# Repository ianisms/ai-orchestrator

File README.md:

# ai-orchestrator

This is a fully local voice assistant. A custom smart speaker built on a Raspberry Pi CM5 talks to a GPU server over one bidirectional gRPC stream. Speech recognition, the language model, tool calling, and speech synthesis all run on hardware in the house. Nothing in the audio path touches a cloud API.

This repository is a sanitized snapshot of a personal project, published as a reference for how I design and build systems. It is not packaged for reuse; there is no one-command install. It does show a working end-to-end system with the tradeoffs left visible. It has streaming everywhere, barge-in, per-speaker identity, an MCP tool plane with authorization boundaries, and observability from the first commit.

I am Ian Bennett ([github.com/ianisms](https://github.com/ianisms)). The source is available for review under the PolyForm Strict License 1.0.0. Any other use needs my written permission. See [LICENSE.md](LICENSE.md) and [NOTICE](NOTICE).

## What is here

| Path | What it is |
|---|---|
| [`server/`](server/README.md) | GPU server: gRPC orchestrator, MCP tools server and proxy, custom TTS service, Docker Compose stack with Prometheus, Grafana, and Loki |
| [`speaker/`](speaker/README.md) | Pi CM5 voice client (wakeword, VAD, capture, playback, barge-in), device tree overlay, bring-up scripts, custom KiCad carrier board, 3D-printed enclosure |
| [`DESIGN_NOTES.md`](DESIGN_NOTES.md) | Design notes with file references |
| [`security/`](security/README.md) | Agent identity and authorization prototypes: token exchange delegation, revocation, a policy check before every tool call with the policy grammar in Rego, voice step-up rules, threat model |

Everything in `server/` is Python 3.11 with `asyncio`, gRPC, FastMCP, FastAPI, and NVIDIA NeMo. The speaker client is Python on Raspberry Pi OS in a Docker container with ALSA passthrough. Hardware sources are KiCad 9 and STEP.

## Architecture

```mermaid
flowchart LR
    subgraph Speaker["Smart speaker (Pi CM5)"]
        MIC[XVF3800 mic array<br/>I2S capture] --> WW[Wakeword<br/>openWakeWord]
        WW --> VAD[Adaptive VAD<br/>+ preroll]
        VAD --> GC[gRPC client]
        GC --> PB[Playback worker<br/>+ barge-in monitor]
        PB --> AMP[JAB5 DSP amp<br/>I2S playback]
    end

    GC <-->|"Converse<br/>bidirectional stream"| ORCH

    subgraph Server["GPU server (Ryzen 9 / RTX PRO 6000)"]
        ORCH[Orchestrator<br/>:7000 gRPC]
        ORCH --> STT[STT<br/>Parakeet CTC NIM]
        ORCH --> LLM[LLM<br/>Qwen3 on vLLM]
        ORCH --> TTS[TTS<br/>FastPitch + HiFi-GAN]
        ORCH <--> TOOLS[Tools server<br/>FastMCP :9102]
        TOOLS --> LOCAL[20 local tools<br/>weather, places, identity, ...]
        TOOLS --> PROXY[MCP proxy]
        PROXY --> HA[Home Assistant<br/>MCP server]
        ORCH -.-> OBS[Prometheus / Grafana / Loki]
        TOOLS -.-> OBS
        TTS -.-> OBS
    end
```

One turn runs end to end like this. The speaker hears the wakeword, plays a chime, and streams 16 kHz PCM frames to the orchestrator. The orchestrator forwards audio to the STT service as it arrives and starts a speculative LLM call on partial transcripts. When the utterance commits, the LLM streams a reply. Any tool calls in it are validated locally, dispatched in parallel over MCP, and folded back into a second low-temperature synthesis pass. Reply text is sanitized for speech and streamed to the TTS service. The TTS service returns PCM that the orchestrator relays to the speaker in chunks. If the user talks over the reply, the speaker detects it, sends `Cancel`, and the server tears down TTS mid-stream.

## Things worth reading

These are the parts I would point a reviewer at first. [`DESIGN_NOTES.md`](DESIGN_NOTES.md) has the full list with file references.

**Audio never crosses the tool protocol.** Speaker identification needs the turn's audio, but base64-encoding seconds of PCM through JSON-RPC is the wrong shape. The orchestrator instead wraps the STT input queue in a duck-typed `AudioTapQueue`. It records frames in passing, writes a WAV on commit, and injects an opaque `[AUDIO_REF session_id audio_id]` into the prompt. The identity tool reads the file from a shared mount. There is zero copy on the hot path, and the reference is bound to this turn so it cannot be replayed. ([`server/modules/orchestrator/core/audio_tap.py`](server/modules/orchestrator/core/audio_tap.py))

**Authorization boundaries the model cannot cross.** Two kinds of state are scoped by values the LLM never supplies. `client_id` for per-device preferences comes from the gRPC peer, and person identity comes from the current turn's audio. The MCP proxy enforces per-upstream `allowed_tools` and `denied_tools`, and deny wins. It namespaces upstream tools as `server__tool` so nothing collides. It unregisters a server's tools when its liveness ping fails, so the model never sees a tool it cannot call. Tool arguments are validated against JSON Schema locally before dispatch. Unknown tool names are dropped and never called. ([`server/tools_server/mcp_proxy.py`](server/tools_server/mcp_proxy.py), [`server/modules/orchestrator/core/utterance.py`](server/modules/orchestrator/core/utterance.py))

**Agent identity prototypes, built next to the assistant.** `security/` holds standalone prototypes for the next layer of that boundary. RFC 8693 token exchange carries the whole agent chain (user > gateway > sub-agent) in an `act` claim. An AuthZEN-shaped policy check in OPA runs before every `tools/call` and fails closed. Voice step-up rules cover the speaker match threshold, home-network origin, liveness, and confirmation on by default and mandatory for high-risk tools. A threat model lists the attacks run against them. The delegation and policy prototypes still run on their own. The voice rules also run inside the orchestrator as a gate in front of every tool call, in monitor mode until the liveness check and approval channels exist ([`server/modules/orchestrator/core/voice_gate.py`](server/modules/orchestrator/core/voice_gate.py)). CI runs the security and voice gate tests on every pull request, and the check is required on `main`. ([`security/README.md`](security/README.md), [`security/THREAT_MODEL.md`](security/THREAT_MODEL.md))

**Hot reload propagated end to end.** Save a tool file on the server and the LLM's tool list updates without restarting anything. `watchfiles` triggers an unregister-then-reload in the tools server. The tools server pushes a `ToolListChangedNotification` to every live MCP transport. The orchestrator's client picks it up and refreshes asynchronously. ([`server/tools_server/loader.py`](server/tools_server/loader.py), [`server/modules/orchestrator/tools/mcp_client.py`](server/modules/orchestrator/tools/mcp_client.py))

**Upstream MCP schemas rewritten from YAML.** Home Assistant's MCP tool descriptions were written for a chat UI. A voice model has to pick `name`, `area` or `floor` in one shot and needs something tighter. `mcp-servers.yaml` overrides descriptions and entire parameter schemas per upstream tool without forking the upstream server, and stamps provenance into tool metadata. The proxy also carries a transport subclass because Home Assistant needs `POST` for its SSE stream. ([`server/tools_server/mcp-servers.yaml`](server/tools_server/mcp-servers.yaml), [`server/tools_server/mcp_proxy.py`](server/tools_server/mcp_proxy.py))

**Degrade before evict.** Under session pressure the orchestrator shrinks every session's history token budget instead of dropping conversations. It only hard-evicts LRU above a separate 1.25x cap. The budget itself is negotiated from the model's real `max_model_len` at startup. Config can lower it but never overflow the context. ([`server/modules/aiserver/server.py`](server/modules/aiserver/server.py))

**Barge-in on both ends.** Server side, any inbound audio frame while `SPEAKING` sets an `asyncio.Event` that doubles as the TTS cancel token. Client side, a dedicated VAD instance watches the mic only during playback. A stale-queue drain and a 600 ms chime-bleed guard keep it from triggering on its own output. The client also has a documented late-cancel path. The receive loop polls the cancel event because the transmit task has already exited after end-of-utterance. ([`speaker/modules/speaker/capture_streamer.py`](speaker/modules/speaker/capture_streamer.py), [`speaker/modules/speaker/grpc_client.py`](speaker/modules/speaker/grpc_client.py))

**Three queues, three overflow policies.** Inbound audio and text drop the oldest. The outbound queue evicts the oldest and records which message kind was dropped. On the speaker, the `control` event topic is unbounded while telemetry topics drop. Losing a wakeword or barge-in event is unacceptable. Losing a stats event is fine. ([`server/modules/aiserver/server.py`](server/modules/aiserver/server.py), [`speaker/modules/speaker/events_bus.py`](speaker/modules/speaker/events_bus.py))

**Prosody-aware TTS streaming.** The TTS service chunks on sentence boundaries and merges tiny trailing fragments backwards because they synthesize badly. It crossfades chunks with an equal-power window and inserts real silence at sentence ends. Text normalization runs under a 150 ms budget and falls back to raw text, so it is never a latency floor. A single GPU lock serializes synthesis because the LLM, STT, and TTS share one card. ([`server/tts/server/`](server/tts/server/))

**Proto drift shows up as a warning.** The server hashes its own `.proto` at startup and exchanges the SHA in gRPC metadata. Skew between the Pi and the server shows up as one log line instead of a deserialization bug three layers down. ([`server/modules/aiserver/server.py`](server/modules/aiserver/server.py))

## Hardware

The speaker is a Raspberry Pi CM5 on a custom carrier board ([`speaker/hardware/pcb/theboard/`](speaker/hardware/pcb/theboard/), KiCad, revision 3.7). An XMOS XVF3800 four-mic array captures over I2S and a Wondom JAB5 (ADAU1701 DSP) amplifier plays back over the same bus. The Pi is bitclock and frame master for both. A single device tree overlay ([`speaker/overlays/xvf3800-jab5-i2s.dts`](speaker/overlays/xvf3800-jab5-i2s.dts)) exposes them as one ALSA card with capture and playback. Power is an internal Mean Well 28 V supply with a captive AC cord. The enclosure ([`speaker/enclosure/`](speaker/enclosure/guide/guide.md)) is 3D printed with a wood veneer wrap. STEP solids and the build guide are included.

[`speaker/README.md`](speaker/README.md) has the wiring table, power architecture, and bring-up sequence.

## Running it

This is not turnkey, but the pieces are all here. The server expects an NVIDIA GPU with enough VRAM for the three inference services, Docker with the NVIDIA container toolkit, and model weights under `/ai/server/` as described in [`server/README.md`](server/README.md). Copy `server/.env.example` to `.env` and fill in the API keys for whichever tools you enable. `docker compose up` in `server/docker/` brings up the stack with health-gated dependency ordering.

The speaker client is built and deployed with `speaker/scripts/build_pi_release.sh` and `deploy_pi_release_wsl.sh`. See [`speaker/README.md`](speaker/README.md).

## What was removed for publication

Secrets were never committed. These were stripped or generalized:

- LAN addresses and hostnames
- personal contact details and example locations
- the local model directory name
- the system prompt persona
- AI coding-assistant session files
- an earlier generation of the speaker client
- PCB revisions 3.5 and 3.6 and the fabrication order files
- large generated artifacts (STEP exports of the PCB, footprint caches)

The custom TTS voice model, the custom wakeword model, and their training data are not included; the wakeword config defaults to a public openWakeWord model. Git history was not carried over.

## Author

Ian Bennett is a principal engineer and architect with 27 years in software, most recently at Microsoft on Azure Identity Governance and Azure Customer Lockbox. This project is where the identity and authorization thinking from that work meets a soldering iron.

## Decisions and division of labor

This repo was built the way I build now. I set the design and the rules. Claude (Claude Code and the Claude app) wrote most of the implementation, tests and docs against those designs. I reviewed, pushed back, and merged. The design calls below are mine. Where an agent proposed something I rejected or changed, the final shape is what is in the tree.

- The model never supplies its own identity. Speaker identity comes from the turn's audio. Origin comes from the device credential the speaker proved with its hardware key, or from the gRPC peer until that is required. Neither ever comes from headers or from anything the model says. Saying "I'm Alice" queues an enrollment sample for out-of-band approval and never changes a profile. New voices are enrolled in an admin-run session with prompted sentences and a separation check against the other voices in the house ([`security/VOICE_ENROLLMENT.md`](security/VOICE_ENROLLMENT.md)).
- The voice gate takes a strong speaker match, device origin and a liveness check as policy inputs. Confirmation is on by default and never waivable for high-risk tools. Unknown tools are treated as writes. Any missing signal denies. It rolled out in monitor mode first, with enforce after calibration, the same way I onboarded services to Customer Lockbox.
- Agents pass delegation, never credentials. Every hop exchanges for its own tokens with its own identity. Scope only narrows down the chain, depth is capped, and tools reject tokens without the `act` chain.
- Revocation cuts the narrowest thing first: a token, then a grant, then a client. The user token's `grant_id` travels unchanged down the chain, so revoking it kills the whole family. That closes a gap Keycloak leaves open. Tool servers can report a token with a reason, and the STS decides whether a report escalates.
- No stored secrets where federation can replace them. A tool that cannot speak OAuth sits behind a proxy that can. The proxy fetches the native credential per call and holds nothing at rest. Every remaining static secret carries a migration date.
- One broker surface for agents, with adapters underneath that use each platform's workload identity where it exists and our own where it does not. Agents never carry per-platform code.
- Device identity for the speaker is a plugged-in YubiKey now, because it ships this month, and then a TPM 2.0 on the PCB of the next carrier-board revision. I design the board, and a part on the board beats a dongle.
- The enclosure design is entirely mine. The CM5 carrier board was a joint effort. I authored the KiCad files, schematic and layout, and Claude advised on component selection.
- Publication is a sanitized single-commit copy of the private repos, with the MAUI client left out and PolyForm Strict in place of MIT so the code is usable only with my consent.

Claims were checked against the tree in both directions. When my description outran the code (the voice gate rules, before the gate existed), the gap became a backlog item and then the prototype. When a doc outran the code (an attestation story that called network origin plus voice "attestation"), the doc was cut back to what is true.

Three things are still unproven. The YubiKey signer has not run on hardware. The device credential is not yet enforced on the gRPC stream. The voice gate is in monitor mode. I would sooner say that here than have you find it.

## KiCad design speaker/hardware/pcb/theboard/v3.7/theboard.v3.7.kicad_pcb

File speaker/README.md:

# Smart speaker

This is the voice client and hardware for a fully local voice assistant. A Raspberry Pi Compute Module 5 on a custom carrier board captures audio from an XMOS XVF3800 mic array over I2S. It streams the audio to the AI server over gRPC and plays the reply through a Wondom JAB5 DSP amplifier on the same I2S bus. There is no cloud dependency anywhere in the audio path.

## Voice flow

1. The client listens continuously for a wakeword with openWakeWord. The deployed unit uses a custom phrase trained with the [openWakeWord training notebook](https://github.com/dscripka/openWakeWord#training-new-models). That model is not included. `wake_model_path` defaults to the bundled `hey_jarvis` model, which `docker/oww_bootstrap.py` downloads at image build.
2. On wake it plays a chime and begins streaming the utterance. A pre-roll buffer keeps the audio from just before the wake event so the first syllable is not clipped.
3. Energy-based adaptive VAD gates the stream. Capture ends on sustained silence, or early when the server reports `THINKING` or sends the first TTS chunk.
4. The server streams `Transcript`, `Reply`, and `TtsAudio` back. Audio is queued to a playback worker and written to ALSA from a dedicated thread.
5. During playback a separate barge-in monitor watches the mic. Sustained speech cancels playback, sends `Cancel` upstream, and starts a new turn with the interrupting audio as its pre-roll.
6. After the reply the client can optionally hold a follow-up window (`followup_enable`) and return to idle on silence.

## Software (`modules/speaker/`)

| File | Role |
|---|---|
| `orchestrator.py` | Wires seven supervised tasks with exponential-backoff restart; `tee_mic()` fans mic frames out to the wakeword, utterance, and barge-in queues and holds the echo suppression and playback-guard policy |
| `capture_streamer.py` | Turn capture. Drain, settle, VAD-gated `mic_iter`, barge-in monitor, playback backpressure |
| `grpc_client.py` | Persistent `Converse` stream, reconnect with backoff, early transmit stop, late-cancel path |
| `vad.py` | RMS VAD with adaptive threshold, noisy-room ceiling, persisted noise floor |
| `audio_capture.py`, `audio_playback.py`, `playback_worker.py` | ALSA capture and playback, threaded writer, out-of-order chunk stash |
| `wake_listener.py`, `wakeword_loop.py` | openWakeWord scoring and chime |
| `events_bus.py`, `state_machine.py` | Topic pub/sub with per-topic overflow policy; guarded state transitions |
| `config.py`, `reload.py` | Flat config dataclass with unknown-key warnings and named benchmark profiles; hot restart on file change |

Configuration is `config/config.yaml`, with `config/benchmarks.yaml` supplying the `latency`, `balanced`, `robust`, and `noisy` profiles. The Docker image (`docker/`) pins gRPC and protobuf and generates the stubs at build time. It pre-downloads the openWakeWord base models so a Pi with no network still boots.

`test/test_speaker_integration.py` covers VAD calibration persistence, speech-versus-silence detection, state machine guards, and event bus isolation with synthesized PCM. `test/test_device_identity.py` covers the device identity pieces below with an in-memory signer. `test/chat_client.py` is a text-mode client for the server. `scripts/test/oww/testit.py` is a standalone wakeword bench.

## Device identity (YubiKey)

Off by default. With `device_identity_enable: true` the client proves at boot that it holds a key the orchestrator enrolled, and gets a short-lived device credential back. The key lives in a YubiKey 5 plugged into the CM5's USB port. It is generated on the YubiKey, so it cannot be copied off the device. Signing does not need a touch, and the PIN is asked for once at boot. `modules/speaker/device_identity.py` holds the `Signer` interface, the `YubiKeyPivSigner`, a `FakeSigner` for tests, and the challenge client. The design, its limits and the TPM on the next board revision are in `security/DEVICE_IDENTITY.md`.

One-time enrollment, on the Pi with the YubiKey in:

```
sudo apt install pcscd                          # host side; the container reaches it over /run/pcscd
printf '%s' "$PIN" > /ai/speaker/state/device_pin && chmod 600 /ai/speaker/state/device_pin
python scripts/enroll_device_key.py generate --device-id speaker-1 --room kitchen --household home \
    --management-key-file /root/.yk_mgmt --pin-file /ai/speaker/state/device_pin
```

That generates the key, exports the public key, and writes `/ai/speaker/state/device_enrollment.json`. Copy that file to the server host and register it with `python server/scripts/enroll_device.py add --request device_enrollment.json`. Registration is a host-side step, like approving a voice enrollment. A device cannot enroll itself over the network. `enroll_device.py revoke speaker-1` cuts a lost key off in one step.

Then uncomment the `/run/pcscd` mount in `docker/docker-compose.yaml`, set `device_identity_enable: true`, and restart the container. The log line `device credential issued` confirms the challenge passed. `connect metadata keys=x-device-credential` confirms the credential is going out on the Converse stream. The orchestrator logs the device id and key thumbprint at connect. With `DEVICE_IDENTITY_REQUIRE` it refuses a stream without one. With `VOICE_GATE_REQUIRE_DEVICE` the voice gate takes the device as its origin signal (`security/SESSION_BINDING.md`). Both switches are off until every speaker attests.

## Hardware

### Components

| Component | Role |
|---|---|
| Raspberry Pi CM5 | Compute, and I2S bitclock and frame master |
| Custom CM5 carrier board (`hardware/pcb/theboard/`, rev 3.7) | Replaces the Geekworm X1500 and separate breakouts. Internal 28 V input, 5 V and 3.3 V rails, PCIe to M.2 NVMe, 40-pin GPIO, 2x10 ribbon header to the mic array, JST I2S link and Micro-Fit power to the amplifier |
| Seeed reSpeaker XVF3800 (XMOS, non-ESP32 variant) | Four-mic array with beamforming, flashed with XMOS I2S firmware, I2S slave on capture |
| Wondom JAB5 (AA-JA33286, ADAU1701 DSP) | I2S slave on playback, Class D amplifier with DSP limiter |
| Mean Well LRS-150-28 | Internal AC-DC supply, captive AC cord, no user-facing connectors |
| Dayton RS100-4 and RS125-4 | Active driver (top) and passive radiator (bottom) |

`hardware/pcb/theboard/specs.md` is the design brief with the power tree, budget, sequencing, headers, and stackup. The KiCad schematic, board, design rules, DRC report, and JLCPCB gerbers for rev 3.7 are included. Earlier revisions are not.

### I2S wiring

| Signal | Pi GPIO / pin | XVF3800 | JAB5 |
|---|---|---|---|
| BCLK | GPIO18 / pin 12 | X0D37 | pin 2 |
| LRCLK | GPIO19 / pin 35 | X0D38 | pin 1 |
| Pi to DAC data | GPIO21 / pin 40 | | pin 3 |
| Mic to Pi data | GPIO20 / pin 38 | X1D00 | |
| MCLK | not used | not used | not used |

All grounds are common. No clock cross-wiring between the two slaves.

### Device tree overlay

`overlays/xvf3800-jab5-i2s.dts` enables the Pi I2S block as clock producer and declares the XVF3800 as a capture codec (`linux,spdif-dir`) and the JAB5 as a playback codec (`linux,spdif-dit`) on one `simple-audio-card` named `XVF3800-JAB5`. No generic or dummy codecs, no MCLK, no HAT EEPROM. The header comments give the `dtc` compile and `config.txt` install steps.

`xvf3800/` holds the bring-up scripts and notes, including two earlier overlay approaches tried before settling on the single duplex overlay.

### Enclosure

`enclosure/guide/guide.md` is the print and assembly guide for revision 16. The enclosure is a 150 mm by 282 mm PETG-CF cylinder, about 1.7 L sealed. The passive radiator is tuned near 65 Hz. It has hex vent clusters top and bottom and an optional veneer wrap. `enclosure/steps/` has the STEP solids for the body, grille, lens, and full assembly. `guide/gen_images.py` renders the cut diagrams.

## Deployment

`scripts/build_pi_release.sh` assembles a release tree. `scripts/deploy_pi_release_wsl.sh` provisions an SD card from WSL, and `scripts/install_pi_release.ps1` mounts the card's partition on Windows so WSL can write it. Set `PI_USER` and `SSH_PUB` for your environment. On the Pi the client runs as a Docker container (`docker/docker-compose.yaml`) with `/dev/snd` passed through. `server_target` in `config/config.yaml` points at the AI server.

## Non-goals

USB audio, HAT EEPROM, MCLK-based designs, generic or dummy codecs, and replacing I2S with USB were all considered and rejected. The point of the design is one I2S bus with the Pi as master and two purpose-built slaves.

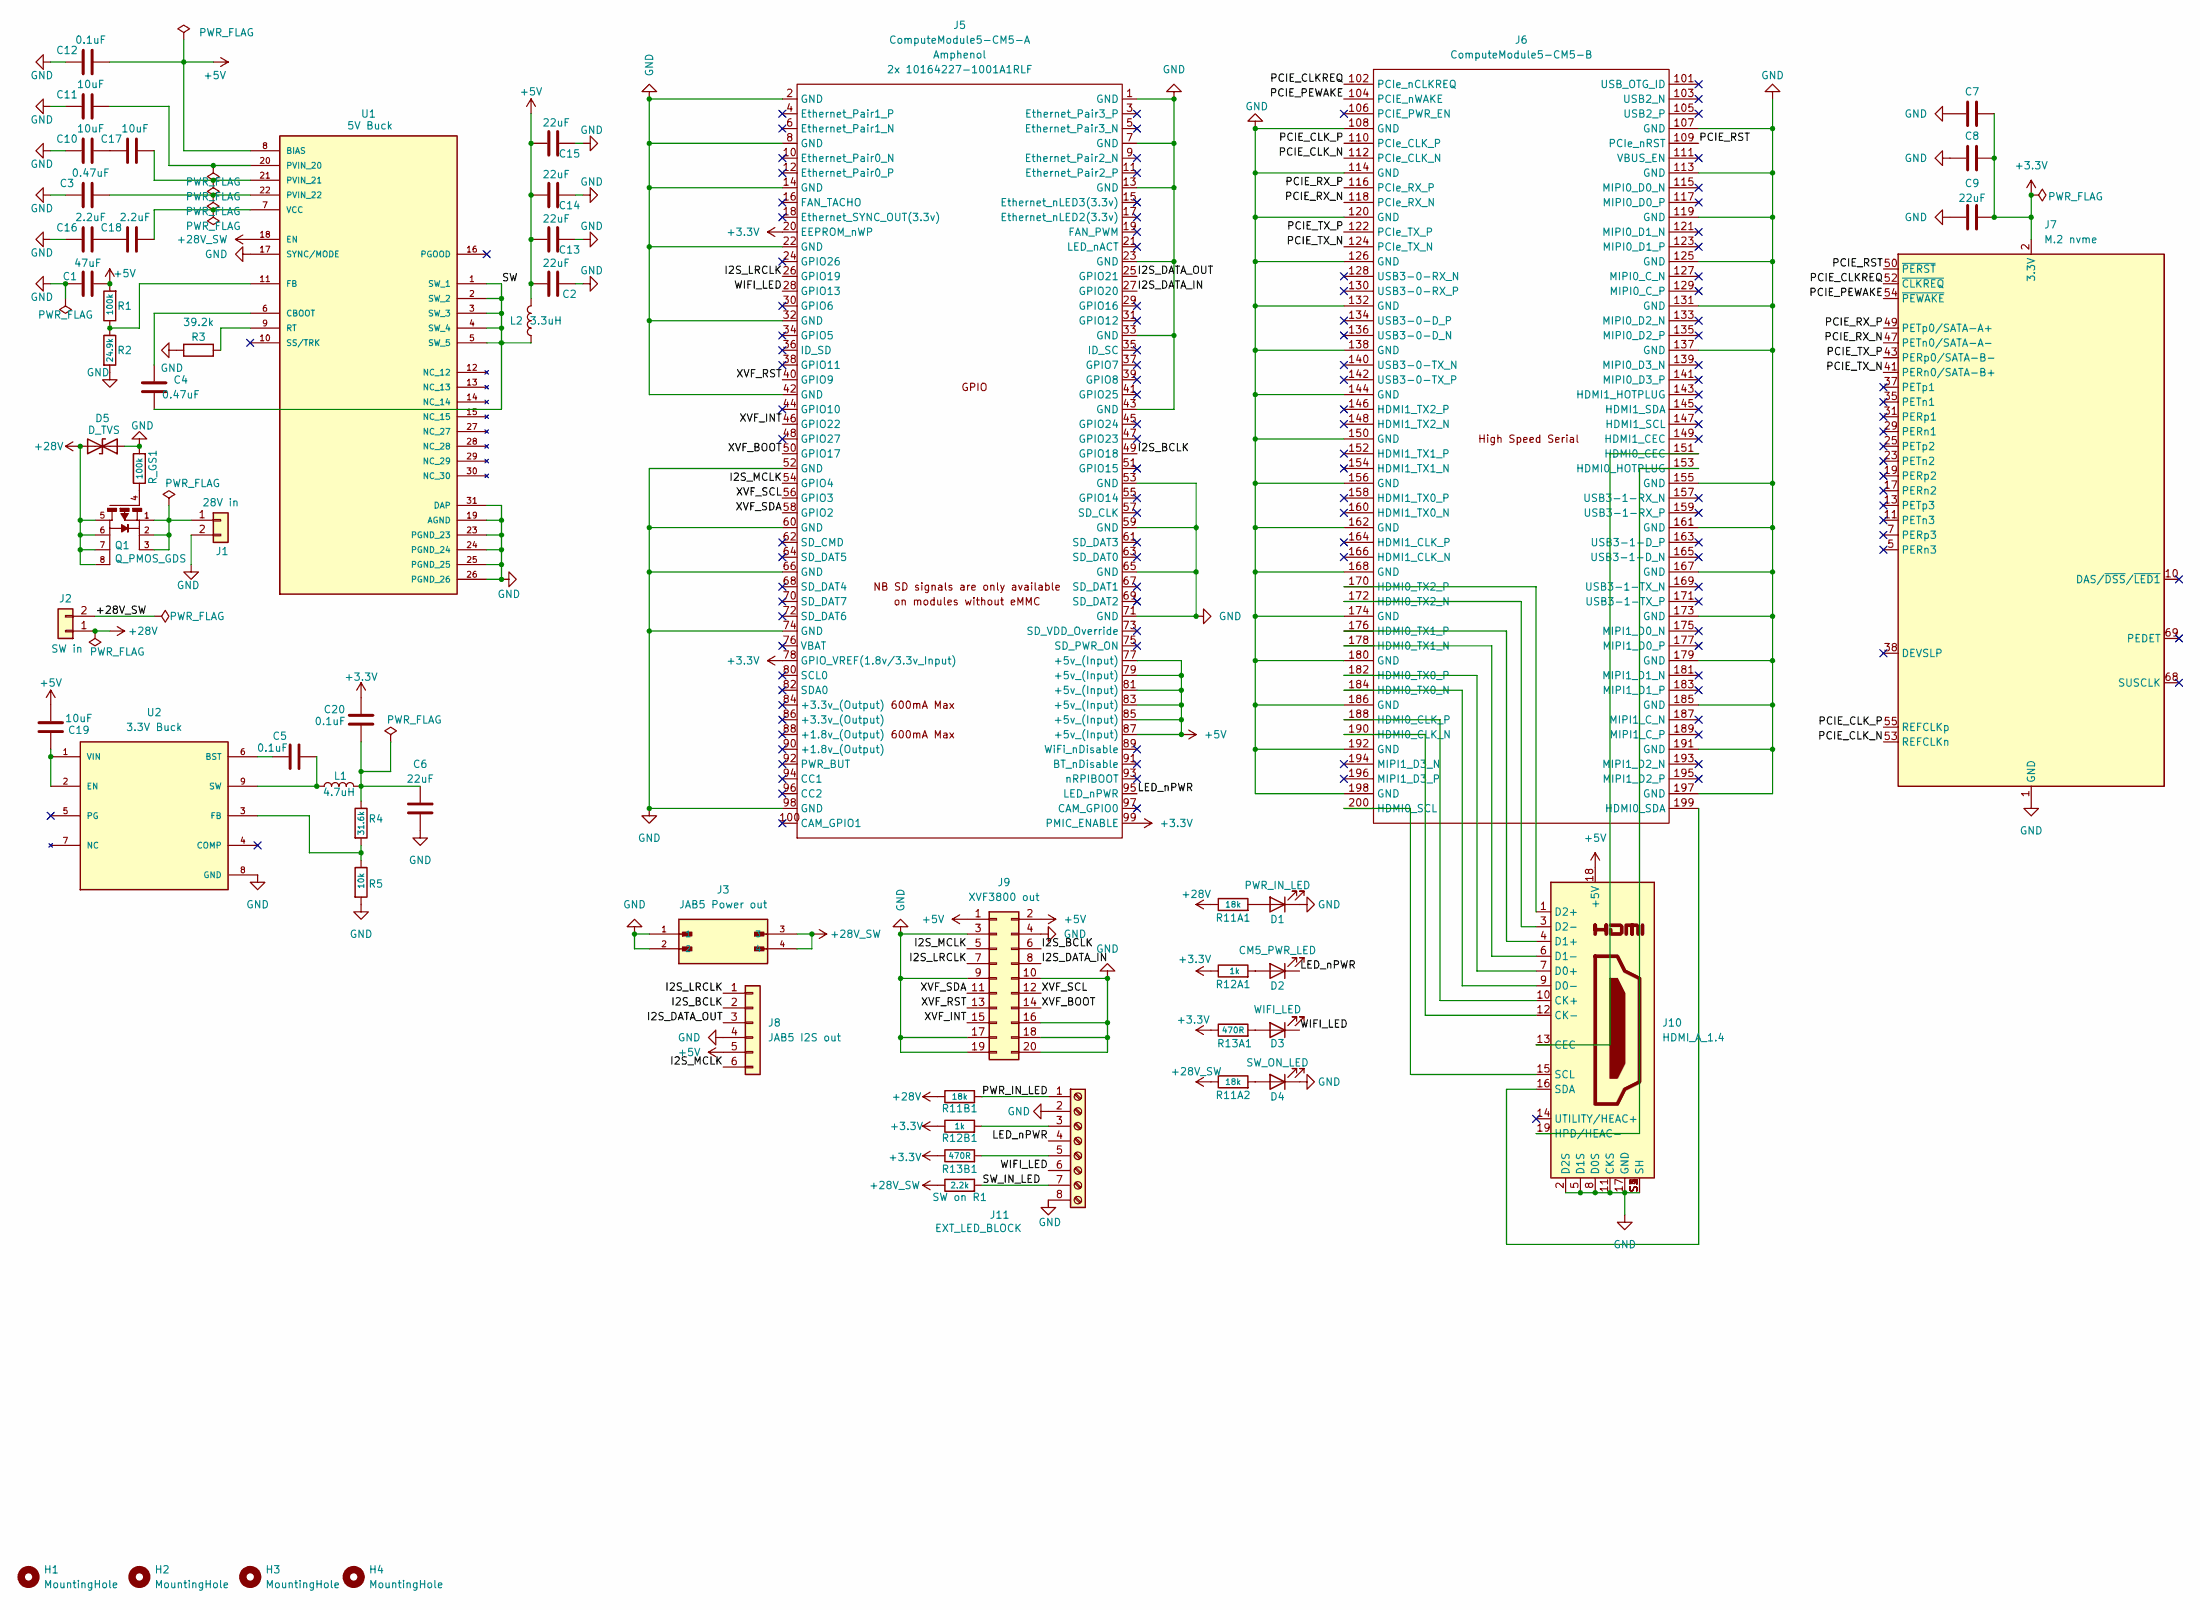
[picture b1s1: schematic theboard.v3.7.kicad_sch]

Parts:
C1: 47uF; C_1210_3225Metric; LCSC C68361
C2, C13, C14, C15: 22uF; C_1206_3216Metric; LCSC C90146
C3: 0.47uF; C_0805_2012Metric; LCSC C335536
C4: 0.47uF; C_0402_1005Metric; LCSC C1571
C5, C7, C8, C20: 0.1uF; C_0402_1005Metric; LCSC C307331
C6, C9: 22uF; C_0805_2012Metric; LCSC C5674
C10, C17: 10uF; C_1210_3225Metric; LCSC C596319
C11, C19: 10uF; C_0805_2012Metric; LCSC C15850
C12: 0.1uF; C_0603_1608Metric; LCSC C14663
C16, C18: 2.2uF; C_0603_1608Metric; LCSC C23630
D1: PWR_IN_LED; LED_0603_1608Metric; LCSC C2286
D2: CM5_PWR_LED; LED_0603_1608Metric; LCSC C2925173
D3: WIFI_LED; LED_0603_1608Metric; LCSC C965807
D4: SW_ON_LED; LED_0603_1608Metric; LCSC C2286
D5: D_TVS; D_SMB; LCSC C178227
H1, H2, H3, H4: MountingHole; MountingHole_2.2mm_M2_Pad_Via
J1: 28V in; MOLEX_430450212; LCSC C3294370
J2: SW in; MOLEX_430450212; LCSC C3294370
J3: JAB5 Power out; MOLEX_39281043; PARTREV M4; LCSC C293502
J5: ComputeModule5-CM5-A; Raspberry-Pi-5-Compute-Module_B; LCSC C597931
J6: ComputeModule5-CM5-B; Raspberry-Pi-5-Compute-Module_A; LCSC C597931
J7: M.2 nvme; M.2 M Key socket; LCSC C841645
J8: JAB5 I2S out; JST_XH_B6B-XH-A_1x06_P2.50mm_Vertical; LCSC C378950
J9: XVF3800 out; IDC-Header_2x10_P2.54mm_Vertical; LCSC C3405
J10: HDMI_A_1.4; TE_1747981-1; LCSC C428484
J11: EXT_LED_BLOCK; JST_PH_B8B-PH-K_1x08_P2.00mm_Vertical; LCSC C157974
L1: 4.7uH; L_Bourns_SRN6045TA; LCSC C963784
L2: 3.3uH; INDM7066X300N; LCSC C2045238
Q1: Q_PMOS_GDS; SI4435DDY; LCSC C10491
R1: 100k; R_0603_1608Metric; LCSC C25803
R2: 24.9k; R_0603_1608Metric; LCSC C25962
R3: 39.2k; R_0603_1608Metric; LCSC C23037
R4: 31.6k; R_0603_1608Metric; LCSC C25967
R5: 10k; R_0603_1608Metric; LCSC C25804
R11A1, R11A2, R11B1: 18k; R_0603_1608Metric; LCSC C25810
R12A1, R12B1: 1k; R_0603_1608Metric; LCSC C21190
R13A1, R13B1: 470R; R_0603_1608Metric; LCSC C23179
R_GS1: 100k; R_0603_1608Metric; LCSC C25803
SW on R1: 2.2k; R_1206_3216Metric; LCSC C25810
U1: 5V Buck; LM73606RNPT; PARTREV 02/2018; LCSC C3198272
U2: 3.3V Buck; CONV_AP63357DV-7; PARTREV 3-2; LCSC C2158014

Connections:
+3.3V: C7.2, C8.2, C9.2, C20.1, J5.20 (EEPROM_nWP), J5.78 (GPIO_VREF(1.8v/3.3v_Input)), J5.99 (PMIC_ENABLE), J7.2 (3.3V), J7.4 (3.3V), J7.12 (3.3V), J7.14 (3.3V), J7.16 (3.3V), J7.18 (3.3V), J7.70 (3.3V), J7.72 (3.3V), J7.74 (3.3V), R12A1.1, R12B1.1, R13A1.1, R13B1.1
+5V: C1.2, C2.1, C12.1, C13.1, C14.1, C15.1, C19.1, J5.77 (+5v_(Input)), J5.79 (+5v_(Input)), J5.81 (+5v_(Input)), J5.83 (+5v_(Input)), J5.85 (+5v_(Input)), J5.87 (+5v_(Input)), J8.5, J9.1, J9.2, J10.18 (+5V), L2.2, R1.2, U1.8 (BIAS); also elsewhere on the board
+28V: D5.2 (A2), J2.1, Q1.5, Q1.6, Q1.7, Q1.8, R11A1.1, R11B1.1
+28V_SW: J2.2, J3.3, J3.4, R11A2.1, SW on R1.1, U1.18 (EN)
/I2S_BCLK: J5.49 (GPIO18), J8.2, J9.6
/I2S_DATA_IN: J5.27 (GPIO20), J9.8
/I2S_DATA_OUT: J5.25 (GPIO21), J8.3
/I2S_LRCLK: J5.26 (GPIO19), J8.1, J9.7
/I2S_MCLK: J5.54 (GPIO4), J8.6, J9.5
/LED_nPWR: D2.1 (K), J5.95 (LED_nPWR), J11.4
/PCIE_CLKREQ: J6.102 (PCIe_nCLKREQ), J7.52 (~CLKREQ)
/PCIE_CLK_N: J6.112 (PCIe_CLK_N), J7.53 (REFCLKn)
/PCIE_CLK_P: J6.110 (PCIe_CLK_P), J7.55 (REFCLKp)
/PCIE_PEWAKE: J6.104 (PCIE_nWAKE), J7.54 (~PEWAKE)
/PCIE_RST: J6.109 (PCIe_nRST), J7.50 (~PERST)
/PCIE_RX_N: J6.118 (PCIe_RX_N), J7.47 (PETn0/SATA-A-)
/PCIE_RX_P: J6.116 (PCIe_RX_P), J7.49 (PETp0/SATA-A+)
/PCIE_TX_N: J6.124 (PCIe_TX_N), J7.41 (PERn0/SATA-B+)
/PCIE_TX_P: J6.122 (PCIe_TX_P), J7.43 (PERp0/SATA-B-)
/PWR_IN_LED: J11.1, R11B1.2
/SW: C4.2, L2.1, U1.1 (SW_1), U1.2 (SW_2), U1.3 (SW_3), U1.4 (SW_4), U1.5 (SW_5); also elsewhere on the board
/SW_IN_LED: J11.7, SW on R1.2
/WIFI_LED: D3.1 (K), J5.28 (GPIO13), J11.6
/XVF_BOOT: J5.50 (GPIO17), J9.14
/XVF_INT: J5.46 (GPIO22), J9.15
/XVF_RST: J5.40 (GPIO9), J9.13
/XVF_SCL: J5.56 (GPIO3), J9.12
/XVF_SDA: J5.58 (GPIO2), J9.11
unnamed: C10.1, C17.2
unnamed: C6.1, C20.2, L1.2, R4.1
unnamed: D1.2 (A), R11A1.2
unnamed: D2.2 (A), R12A1.2
unnamed: D3.2 (A), R13A1.2
unnamed: D4.2 (A), R11A2.2
unnamed: J1.1, Q1.1, Q1.2, Q1.3
unnamed: J6.151 (HDMI0_CEC), J10.13 (CEC)
unnamed: J6.188 (HDMI0_CLK_P), J10.10 (CK+)
unnamed: J6.190 (HDMI0_CLK_N), J10.12 (CK-)
unnamed: J6.182 (HDMI0_TX0_P), J10.7 (D0+)
unnamed: J6.184 (HDMI0_TX0_N), J10.9 (D0-)
unnamed: J6.176 (HDMI0_TX1_P), J10.4 (D1+)
unnamed: J6.178 (HDMI0_TX1_N), J10.6 (D1-)
unnamed: J6.170 (HDMI0_TX2_P), J10.1 (D2+)
unnamed: J6.172 (HDMI0_TX2_N), J10.3 (D2-)
unnamed: J6.153 (HDMI0_HOTPLUG), J10.19 (HPD/HEAC-)
unnamed: J6.200 (HDMI0_SCL), J10.15 (SCL)
unnamed: J6.199 (HDMI0_SDA), J10.16 (SDA)
unnamed: J11.3, R12B1.2
unnamed: J11.5, R13B1.2
unnamed: Q1.4, R_GS1.1
unnamed: C4.1, U1.6 (CBOOT)
unnamed: R1.1, R2.1, U1.11 (FB)
unnamed: C11.1, U1.20 (PVIN_20)
unnamed: C17.1, U1.21 (PVIN_21)
unnamed: C3.1, U1.22 (PVIN_22)
unnamed: R3.1, U1.9 (RT)
unnamed: C5.1, U2.6 (BST)
unnamed: C19.2, U2.1 (VIN), U2.2 (EN)
unnamed: R4.2, R5.1, U2.3 (FB)
unnamed: C5.2, L1.1, U2.9 (SW)

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
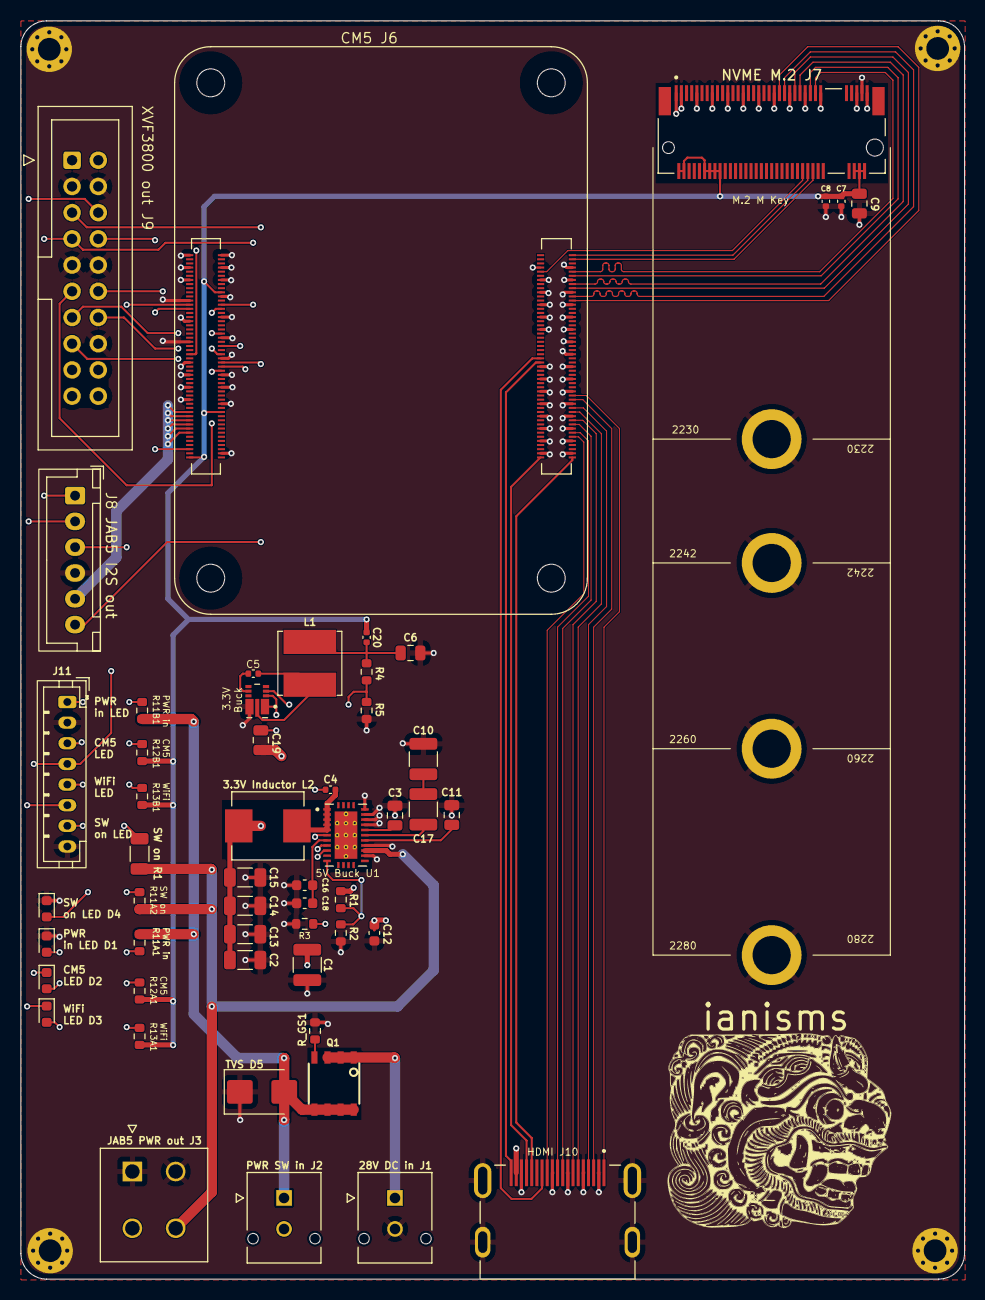
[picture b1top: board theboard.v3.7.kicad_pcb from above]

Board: 6 copper layers, 91.4 x 121.9 mm, 58 parts (0 on the bottom side), 62 nets.

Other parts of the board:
3.3V Inductor L2: 3.3uH; INDM7066X300N

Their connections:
+5V: 3.3V Inductor L2.2; also elsewhere on the board
/SW: 3.3V Inductor L2.1; also elsewhere on the board

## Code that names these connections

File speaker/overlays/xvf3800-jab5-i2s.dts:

/*
 * Device Tree Overlay for XVF3800 + JAB5 I2S Audio
 *
 * Raspberry Pi 5 as I2S master (bitclock + frame master)
 * - XVF3800 mic array: I2S slave, capture (DIN <- GPIO20)
 * - Wondom JAB5 (ADAU1701): I2S slave, playback (DOUT -> GPIO21)
 *
 * GPIO Pinout:
 *   GPIO18 (Pin 12) = BCLK
 *   GPIO19 (Pin 35) = LRCLK / FS
 *   GPIO20 (Pin 38) = DIN (Pi receives from XVF3800)
 *   GPIO21 (Pin 40) = DOUT (Pi sends to JAB5)
 *
 * No MCLK is used.
 *
 * Compile:
 *   dtc -@ -I dts -O dtb -o xvf3800-jab5-i2s.dtbo xvf3800-jab5-i2s.dts
 *
 * Install:
 *   sudo cp xvf3800-jab5-i2s.dtbo /boot/firmware/overlays/
 *
 * config.txt:
 *   dtparam=i2s=on
 *   dtoverlay=xvf3800-jab5-i2s
 */

/dts-v1/;
/plugin/;

/ {
    compatible = "brcm,bcm2712", "brcm,bcm2835";

    /* Fragment 0: Enable rp1_i2s0 as clock producer (Pi is master) */
    fragment@0 {
        target = <&i2s_clk_producer>;
        __overlay__ {
            status = "okay";
        };
    };

    /* Fragment 1: Create the codec nodes */
    fragment@1 {
        target-path = "/";
        __overlay__ {
            /* Playback codec: generic I2S transmitter (Pi -> JAB5) */
            codec_playback: spdif-transmitter {
                #sound-dai-cells = <0>;
                compatible = "linux,spdif-dit";
                status = "okay";
            };

            /* Capture codec: generic I2S receiver (XVF3800 -> Pi) */
            codec_capture: spdif-receiver {
                #sound-dai-cells = <0>;
                compatible = "linux,spdif-dir";
                status = "okay";
            };
        };
    };

    /* Fragment 2: Configure the sound card with duplex dai-links */
    fragment@2 {
        target = <&sound>;
        __overlay__ {
            compatible = "simple-audio-card";
            simple-audio-card,name = "XVF3800-JAB5";
            status = "okay";

            /* Playback link: Pi -> JAB5 */
            simple-audio-card,dai-link@0 {
                reg = <0>;
                format = "i2s";

                /* Pi is master */
                bitclock-master = <&cpu_playback>;
                frame-master = <&cpu_playback>;

                cpu_playback: cpu {
                    sound-dai = <&i2s_clk_producer>;
                    dai-tdm-slot-num = <2>;
                    dai-tdm-slot-width = <32>;
                };

                codec_pb: codec {
                    sound-dai = <&codec_playback>;
                };
            };

            /* Capture link: XVF3800 -> Pi */
            simple-audio-card,dai-link@1 {
                reg = <1>;
                format = "i2s";

                /* Pi is master */
                bitclock-master = <&cpu_capture>;
                frame-master = <&cpu_capture>;

                cpu_capture: cpu {
                    sound-dai = <&i2s_clk_producer>;
                    dai-tdm-slot-num = <2>;
                    dai-tdm-slot-width = <32>;
                };

                codec_cap: codec {
                    sound-dai = <&codec_capture>;
                };
            };
        };
    };
};
